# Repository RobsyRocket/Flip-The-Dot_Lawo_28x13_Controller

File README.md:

# Flip-The-Dot Lawo 28x13 Controller
PCB to carry an FP2800a IC and connect it with a microcontroller of your choice to a flip-dot matrix with a 28x13 resolution made by Lawo.

More [details about the actual hardware](https://github.com/RobsyRocket/Flip-The-Dot/tree/master/Documentation/Hardware/Display%20-%20Lawo%2028x13) and software to drive it can be found in the repository of the parent project called [Flip-The-Dot](https://github.com/RobsyRocket/Flip-The-Dot).

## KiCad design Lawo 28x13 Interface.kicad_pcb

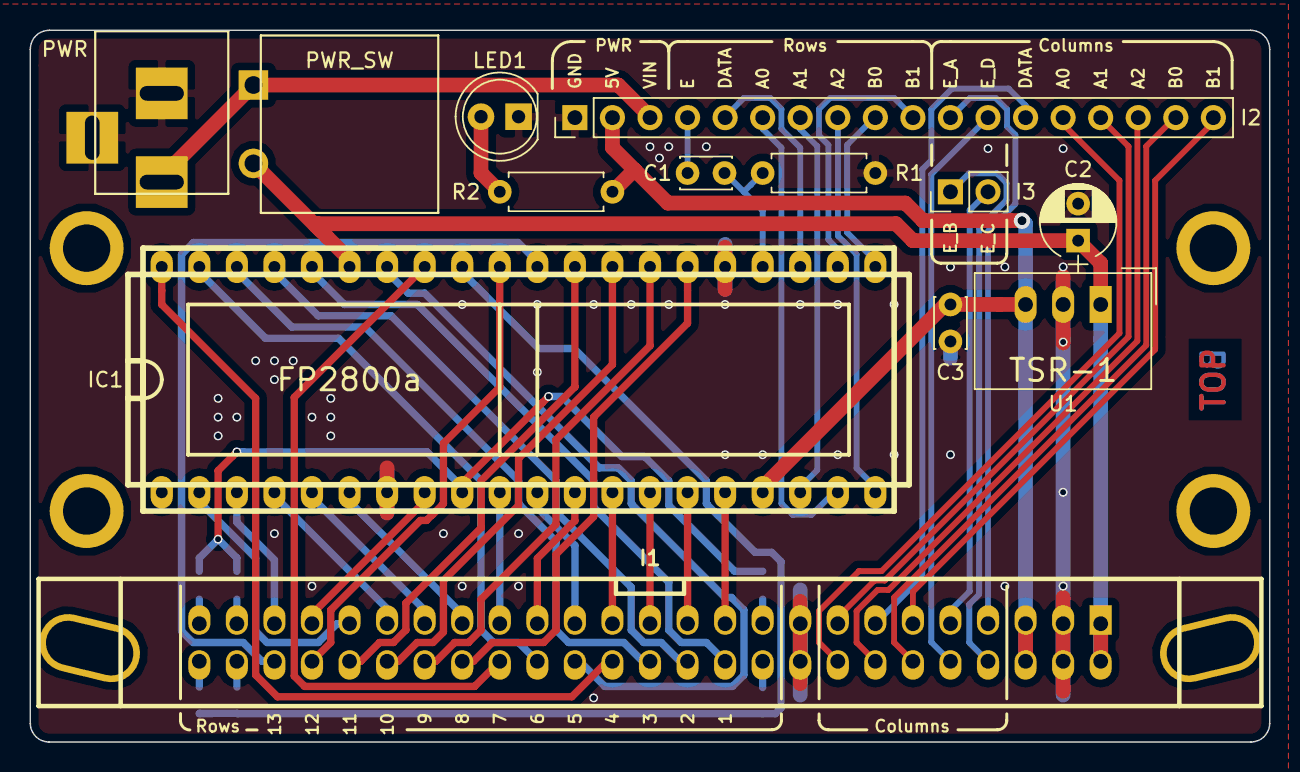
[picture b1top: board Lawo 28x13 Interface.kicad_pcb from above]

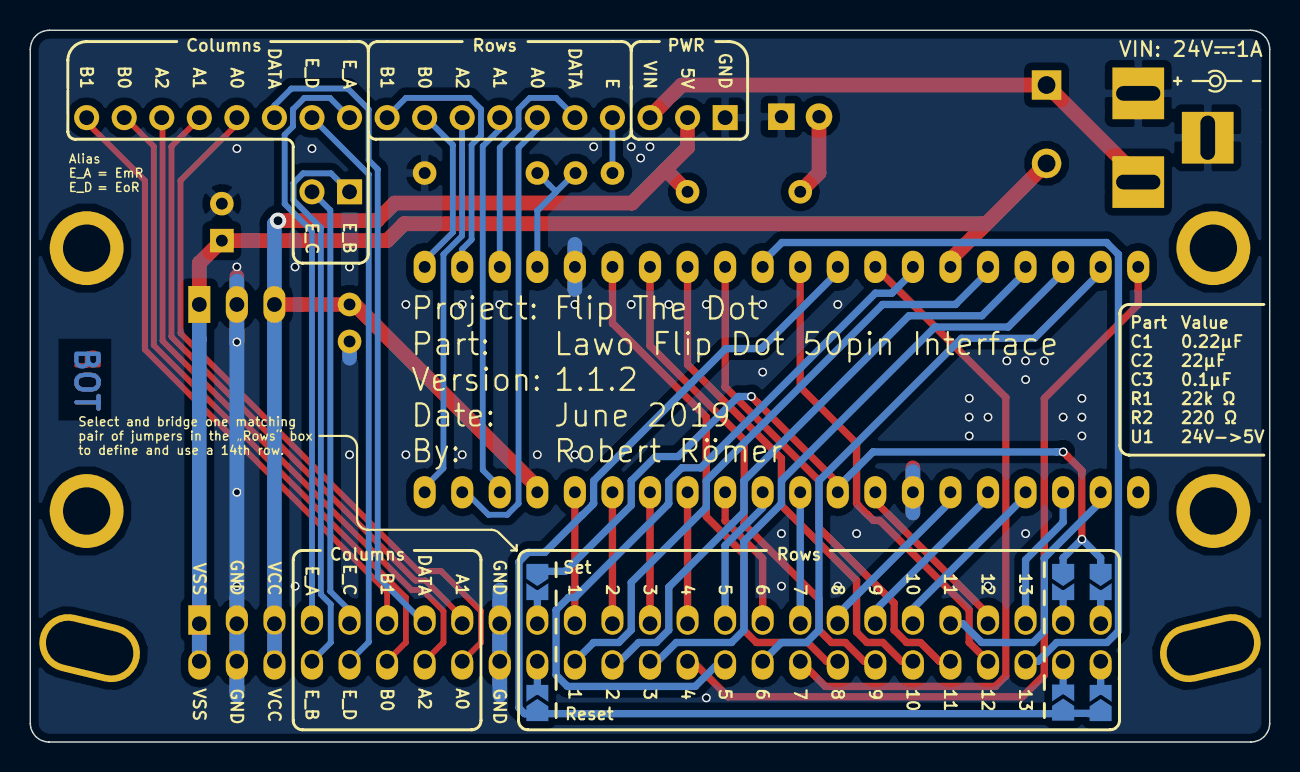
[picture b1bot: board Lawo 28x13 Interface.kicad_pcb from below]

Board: 2 copper layers, 83.8 x 48.1 mm, 23 parts (6 on the bottom side), 57 nets.

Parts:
C1: 0.22μF; C_Disc_D3.4mm_W2.1mm_P2.50mm
C2: 22μF; CP_Radial_D5.0mm_P2.50mm
C3: 0.1μF; C_Disc_D3.4mm_W2.1mm_P2.50mm
I1: Flipdot Interface; psl_50_25x2_strip_with_levers
I2: Control Interface; Socket_Strip_Straight_1x18_Pitch2.54mm
I3: Spare Enable; Socket_Strip_Straight_1x02_Pitch2.54mm
IC1: FP2800a; dil_40-600_socket
J1, J2, J3, J4, J5, J6: Solder_Jumper; SolderJumper-2_P1.3mm_Open_TrianglePad1.0x1.5mm
LED1: Led; LED_D5.0mm
MTH1, MTH2, MTH3, MTH4: 1pin
PWR1: BARREL_JACK
PWR_SW1: Power Switch; SW_PUSH
R1: 22K; R_Axial_DIN0207_L6.3mm_D2.5mm_P7.62mm_Horizontal
R2: 220; R_Axial_DIN0207_L6.3mm_D2.5mm_P7.62mm_Horizontal
U1: TSR-1; DCDC-Conv_TRACO_TSR-1

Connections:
+5V: C3.1, I1.5, I1.6, I2.2, IC1.17, R2.1, U1.3
+24V: C2.1, I1.1, I1.2, IC1.35, PWR_SW1.2, U1.1
COL_A0: I1.16, I2.14
COL_A1: I1.15, I2.15
COL_A2: I1.14, I2.16
COL_B0: I1.12, I2.17
COL_B1: I1.11, I2.18
COL_DATA: I1.13, I2.13
COL_ENABLE_A: I1.7, I2.11
COL_ENABLE_B: I1.8, I3.1
COL_ENABLE_C: I1.9, I3.2
COL_ENABLE_D: I1.10, I2.12
GND: C2.2, C3.2, I1.3, I1.4, I1.17, I1.18, I2.1, IC1.7, IC1.25, LED1.1, PWR1.2, PWR1.3, R1.2, U1.2
unnamed: C1.2, IC1.24, R1.1
unnamed: I1.19, J1.2
unnamed: I1.20, J4.2
unnamed: I1.47, J2.2
unnamed: I1.48, J5.2
unnamed: I1.49, J3.2
unnamed: I1.50, J6.2
unnamed: LED1.2, R2.2
RESET_1: I1.21, IC1.16
RESET_2: I1.23, IC1.15
RESET_3: I1.25, IC1.14
RESET_4: I1.27, IC1.13
RESET_5: I1.29, IC1.11
RESET_6: I1.31, IC1.12
RESET_7: I1.33, IC1.10
RESET_8: I1.35, IC1.6
RESET_9: I1.37, IC1.5
RESET_10: I1.39, IC1.4
RESET_11: I1.41, IC1.2
RESET_12: I1.43, IC1.8
RESET_13: I1.45, IC1.3
RESET_X: IC1.9, J1.1, J2.1, J3.1
ROW_A0: I2.6, IC1.19
ROW_A1: I2.7, IC1.18
ROW_A2: I2.8, IC1.20
ROW_B0: I2.9, IC1.21
ROW_B1: I2.10, IC1.22
ROW_DATA: I2.5, IC1.23
ROW_ENABLE: C1.1, I2.4
SET_1: I1.22, IC1.36
SET_2: I1.24, IC1.37
SET_3: I1.26, IC1.38
SET_4: I1.28, IC1.40
SET_5: I1.30, IC1.34
SET_6: I1.32, IC1.39
SET_7: I1.34, IC1.33
SET_8: I1.36, IC1.26
SET_9: I1.38, IC1.27
SET_10: I1.40, IC1.28
SET_11: I1.42, IC1.29
SET_12: I1.44, IC1.31
SET_13: I1.46, IC1.30
SET_X: IC1.32, J4.1, J5.1, J6.1
VIN: I2.3, PWR1.1, PWR_SW1.1

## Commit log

2019-01-29 initial commit of PCB files - Work In Progress
    - layout not fully verified
    - additional libraries not included
2019-02-11 Updated schematic for upgraded KiCad version and rework of many traces and pin assignments
    - KiCad version upgrade
    - EESchema Schematic File Version 4
    - KiCad 5.0.0-rc3-dev
    - symbols and footprint exchanged to newer versions
    - board changes
    - changed pin assignments for the set pins (swapped group of FP2800a 2a-g and 3a-g)
2019-04-26 Renaming of all files by changing "Lawo 28x13" to "Lawo 28x13 Interface" to clarify its use compared to the Lawo flip-dot module itself.
2019-04-26 minor PCB updates
    - mounting holes are not connected to GND anymore
    - one trace and some Vias moved a little bit
    - updated/added Silkscreen texts (outlines, parts legend and text related to TSR-1, EyR, and EzR)
    - updated plots for the PCB
    - new plots for the schematic and PCB images without rendered parts
2019-05-24 closes #2 by adding KiCad library for the FP2800a IC as git submodule and adjusting path in sym-lib-table
    additional changes:
    - removal of TSR-1 lib reference as it is not needed anymore, existing KiCad symbol already in use
    - removal of rescue lib reference as it is not used and not committed
2019-08-18 Renamed enable pins and slightly modified traces and silk screen.
